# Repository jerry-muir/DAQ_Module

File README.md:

# Data Acquisition Module

## About
An exploration of Data Acquisition using Arduino based HW. In this case, the Atmega32u4 microcontroller.
This prototype consists of a custom USB connected board along with firmware and user interface software.

## The Project

Hardware design files are located at: [Hardware](/Hardware)
<br />
Arduino sketch firmware design files are located at: [Basic DAQ](/Software/Embedded/Arduino/DAQ%20Module/Basic%20DAQ)
<br />
Desktop Software design files are located at:  [BDAQ-6104 Instrument Driver](/Software/LabView/BDAQ-6104%20Instrument%20Driver)

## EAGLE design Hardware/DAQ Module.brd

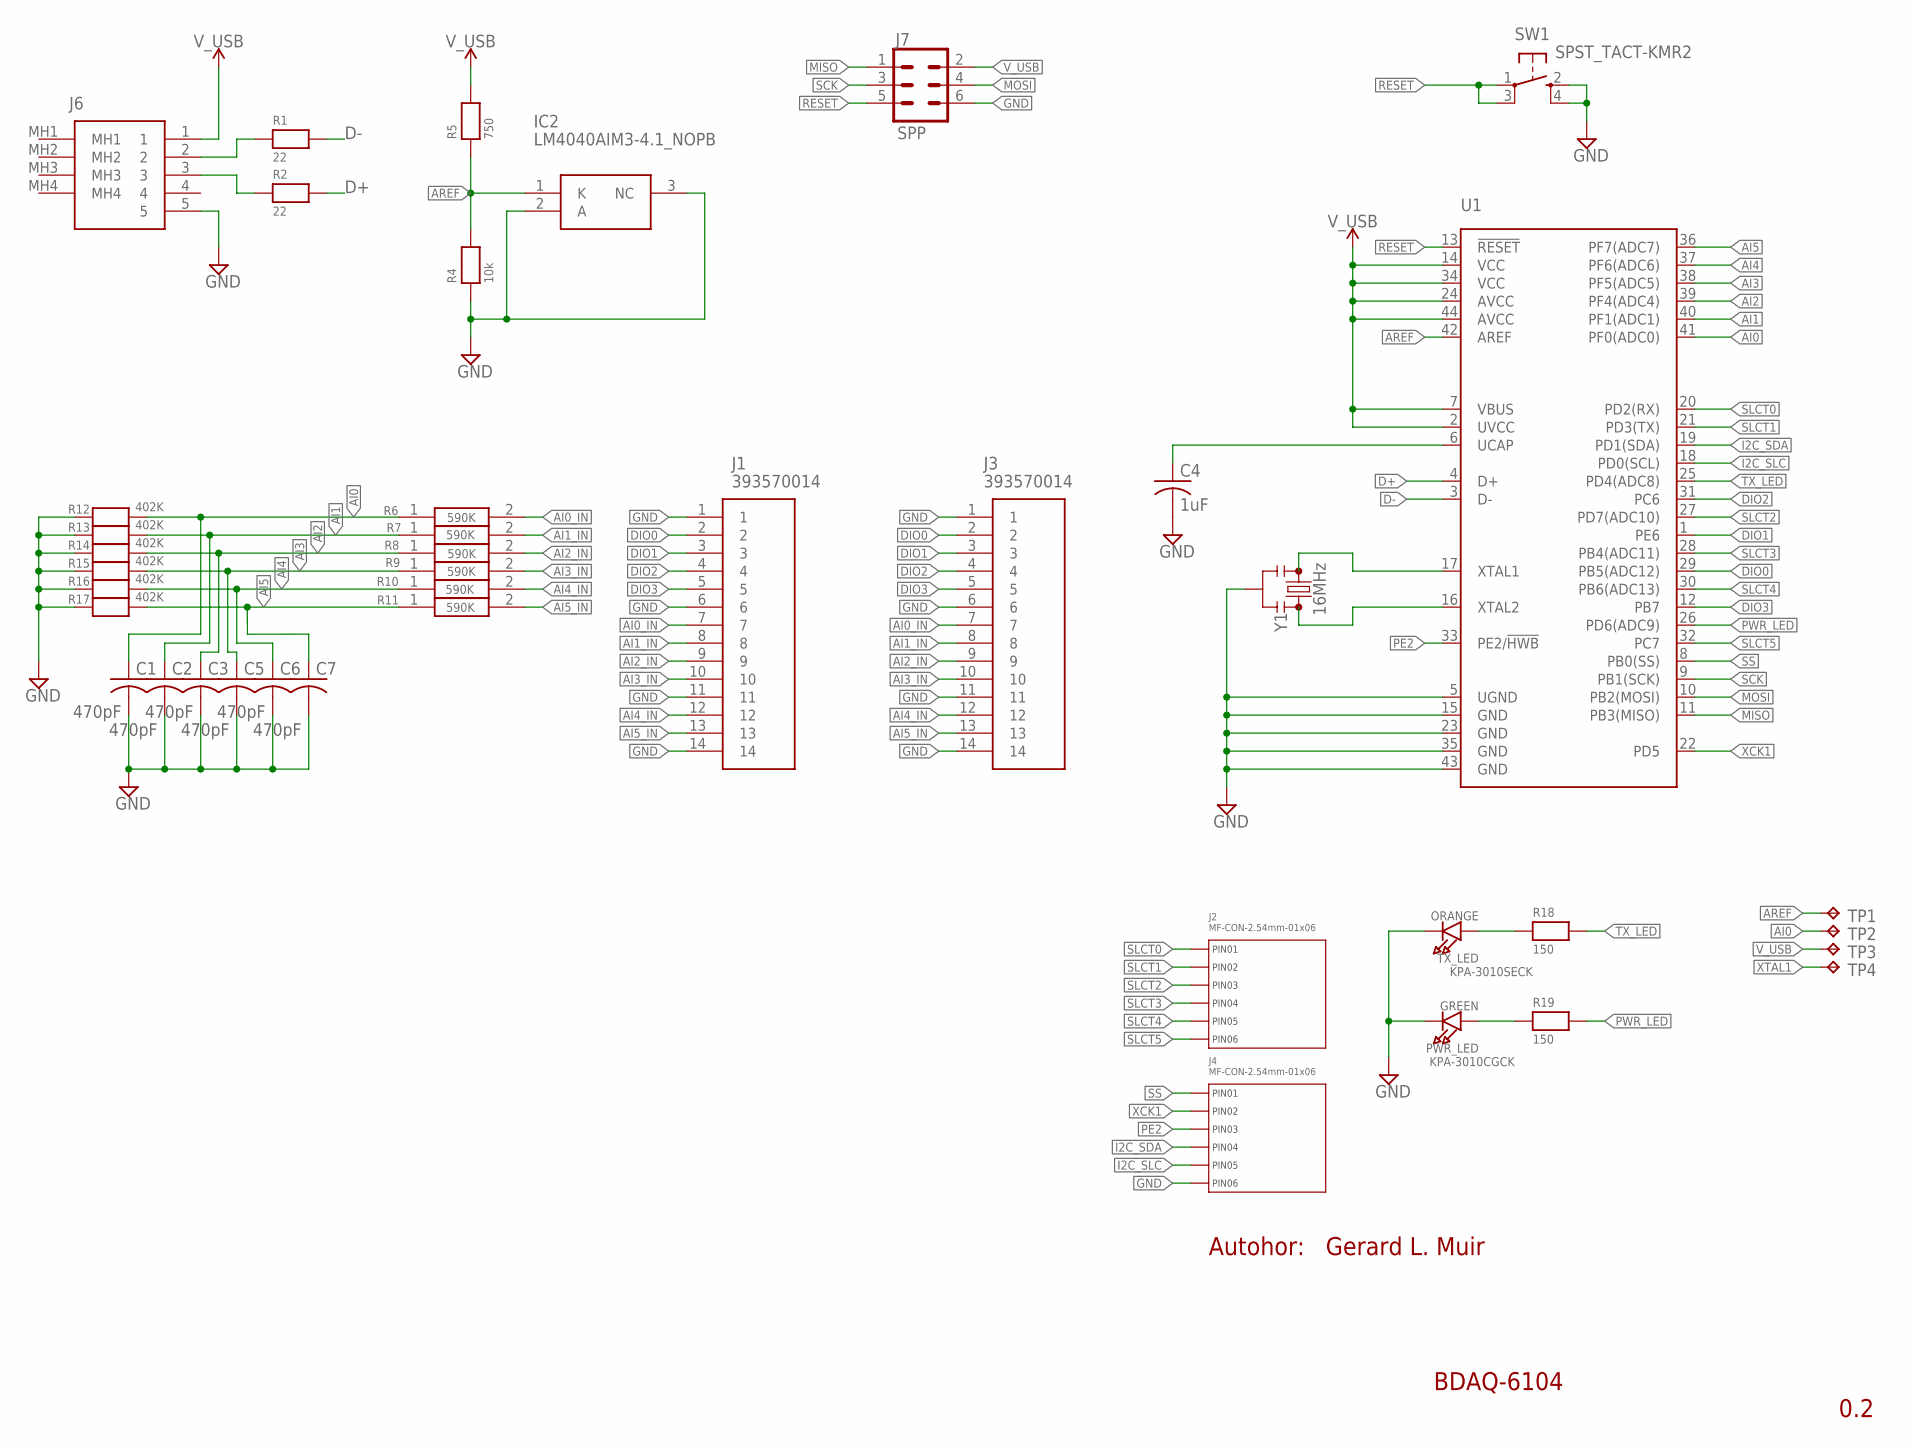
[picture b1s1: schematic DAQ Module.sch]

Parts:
C1, C2, C3, C5, C6, C7: 470pF; C1206; MANUFACTURER_PART C1206C471J5GACTU
C4: 1uF; C1206; MANUFACTURER_PART C3216X7R1E105K085AACopied
IC2: LM4040AIM3-4.1_NOPB; SOT95P237X112-3N
J1: 393570014; RHDR16W90P0X350_1X14_5600X729X
J2, J4: MF-CON-2.54mm-01x06; PTH_2.54MM_01X06
J3: 393570014; 393570014X350_1X14
J6: UJ2-MIBH2-4-SMT-TR; UJ2MIBH24SMTTR
J7: SPP; 2X3
PWR_LED: GREEN; CHIPLED_1206; MANUFACTURER_PART KPA-3010CGCK
R1: 22; 1206; MANUFACTURER_PART ERJ8ENF22R0V
R2: 22; 1206
R4: 10k; 1206; MANUFACTURER_PART RP1206BRD075K1L
R5: 750; 1206; MANUFACTURER_PART MC009121
R6, R7, R8, R9, R10, R11: 590K; RESC1608X55N; MANUFACTURER_PART RNCS1206BKE1M00
R12, R13, R14, R15, R16, R17: 402K; 1206; MANUFACTURER_PART MCWF12R4023BTL
R18: 150; 1206; MANUFACTURER_PART CRCW1206150RFKEA
R19: 150; 1206
SW1: SPST_TACT-KMR2; KMR2; MANUFACTURER_PART KMR221G LFS
TP1, TP2, TP3, TP4: TPB1,27; B1,27
TX_LED: ORANGE; CHIPLED_1206; MANUFACTURER_PART KPA-3010SECK
U1: ATMEGA32U4TQFP; SPARKFUN-DIGITALIC_TQFP44; MANUFACTURER_PART ATMEGA32U4-AU
Y1: 16MHz; RESONATOR-SMD-3.2X1.3; MANUFACTURER_PART CSTNE16M0V530000R0

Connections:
AI0: C1.1, R6.1, R12.2, TP2.TP, U1.41 (PF0(ADC0))
AI0_IN: J1.7, J3.7, R6.2
AI1: C2.1, R7.1, R13.2, U1.40 (PF1(ADC1))
AI1_IN: J1.8, J3.8, R7.2
AI2: C3.1, R8.1, R14.2, U1.39 (PF4(ADC4))
AI2_IN: J1.9, J3.9, R8.2
AI3: C5.1, R9.1, R15.2, U1.38 (PF5(ADC5))
AI3_IN: J1.10, J3.10, R9.2
AI4: C6.1, R10.1, R16.2, U1.37 (PF6(ADC6))
AI4_IN: J1.12, J3.12, R10.2
AI5: C7.1, R11.1, R17.2, U1.36 (PF7(ADC7))
AI5_IN: J1.13, J3.13, R11.2
AREF: IC2.1 (K), R4.2, R5.1, TP1.TP, U1.42 (AREF)
D+: R2.2, U1.4 (D+)
D-: R1.2, U1.3 (D-)
DIO0: J1.2, J3.2, U1.29 (PB5(ADC12))
DIO1: J1.3, J3.3, U1.1 (PE6)
DIO2: J1.4, J3.4, U1.31 (PC6)
DIO3: J1.5, J3.5, U1.12 (PB7)
GND: C1.2, C2.2, C3.2, C4.2, C5.2, C6.2, C7.2, IC2.2 (A), IC2.3 (NC), J1.1, J1.6, J1.11, J1.14, J3.1, J3.6, J3.11, J3.14, J4.P$6 (PIN6), J6.5, J7.6, PWR_LED.C, R4.1, R12.1, R13.1, R14.1, R15.1, R16.1, R17.1, SW1.2 (S), SW1.4 (S1), TX_LED.C, U1.5 (UGND), U1.15 (GND), U1.23 (GND), U1.35 (GND), U1.43 (GND), Y1.2
I2C_SDA: J4.P$4 (PIN4), U1.19 (PD1(SDA))
I2C_SLC: J4.P$5 (PIN5), U1.18 (PD0(SCL))
MISO: J7.1, U1.11 (PB3(MISO))
MOSI: J7.4, U1.10 (PB2(MOSI))
unnamed: J6.2, R1.1
unnamed: J6.3, R2.1
unnamed: C4.1, U1.6 (UCAP)
unnamed: R18.1, TX_LED.A
unnamed: PWR_LED.A, R19.1
PE2: J4.P$3 (PIN3), U1.33 (PE2/!HWB)
PWR_LED: R19.2, U1.26 (PD6(ADC9))
RESET: J7.5, SW1.1, SW1.3 (P1), U1.13 (!RESET)
SCK: J7.3, U1.9 (PB1(SCK))
SLCT0: J2.P$1 (PIN1), U1.20 (PD2(RX))
SLCT1: J2.P$2 (PIN2), U1.21 (PD3(TX))
SLCT2: J2.P$3 (PIN3), U1.27 (PD7(ADC10))
SLCT3: J2.P$4 (PIN4), U1.28 (PB4(ADC11))
SLCT4: J2.P$5 (PIN5), U1.30 (PB6(ADC13))
SLCT5: J2.P$6 (PIN6), U1.32 (PC7)
SS: J4.P$1 (PIN1), U1.8 (PB0(SS))
TX_LED: R18.2, U1.25 (PD4(ADC8))
V_USB: J6.1, J7.2, R5.2, TP3.TP, U1.2 (UVCC), U1.7 (VBUS), U1.14 (VCC), U1.24 (AVCC), U1.34 (VCC), U1.44 (AVCC)
XCK1: J4.P$2 (PIN2), U1.22 (PD5)
XTAL1: TP4.TP, U1.17 (XTAL1), Y1.3
XTAL2: U1.16 (XTAL2), Y1.1

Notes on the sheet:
Gerard L. Muir
0.2
Autohor:
BDAQ-6104

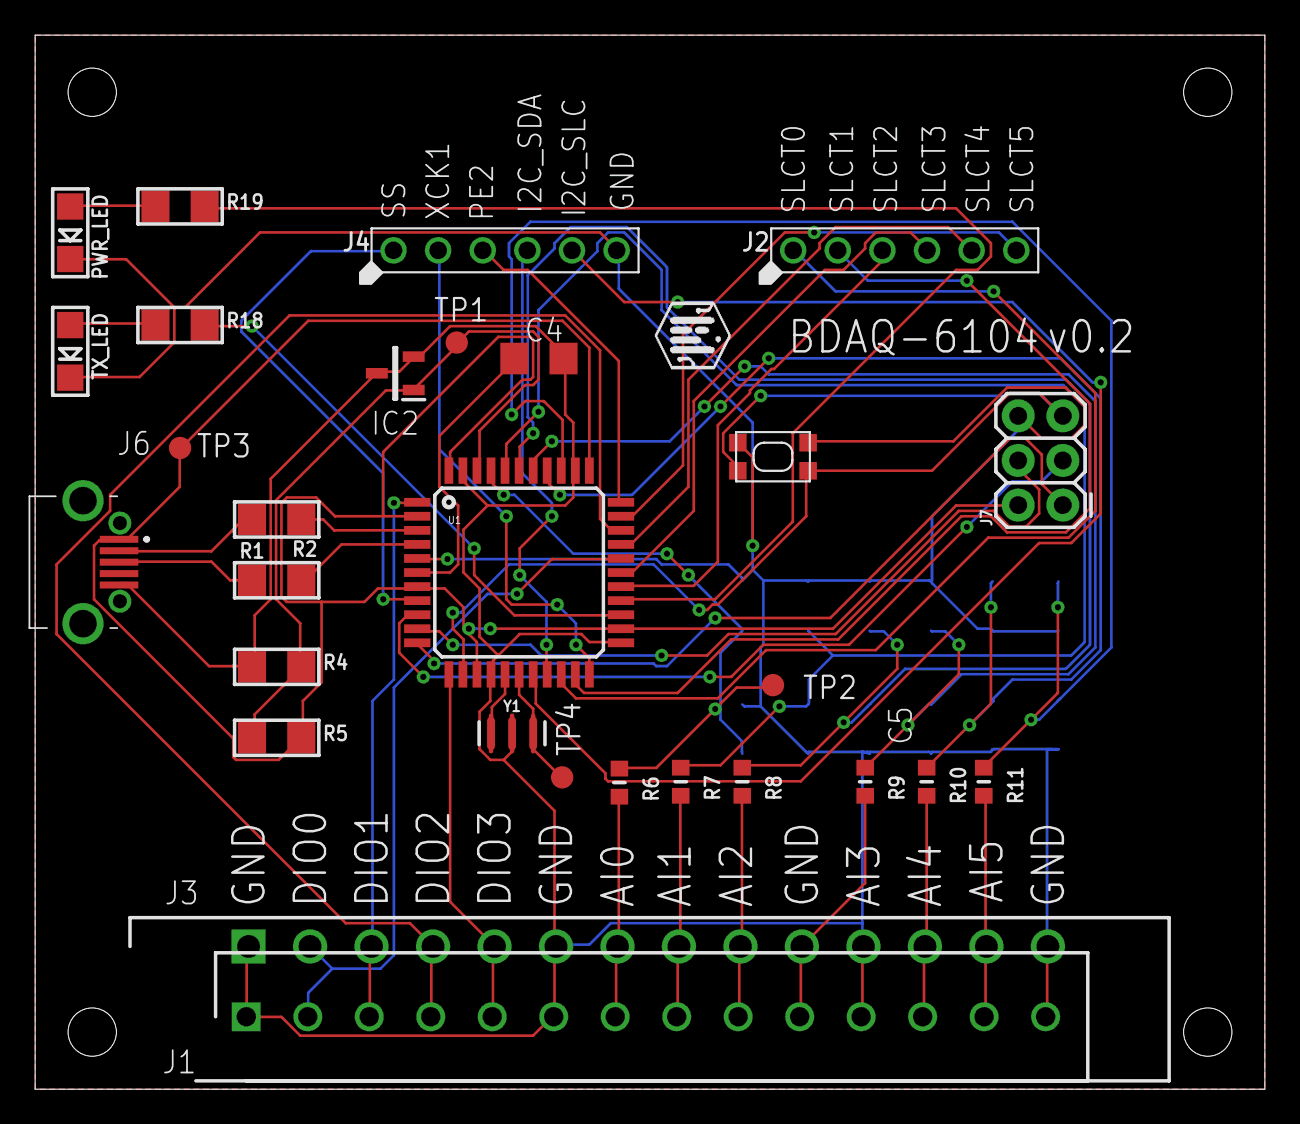
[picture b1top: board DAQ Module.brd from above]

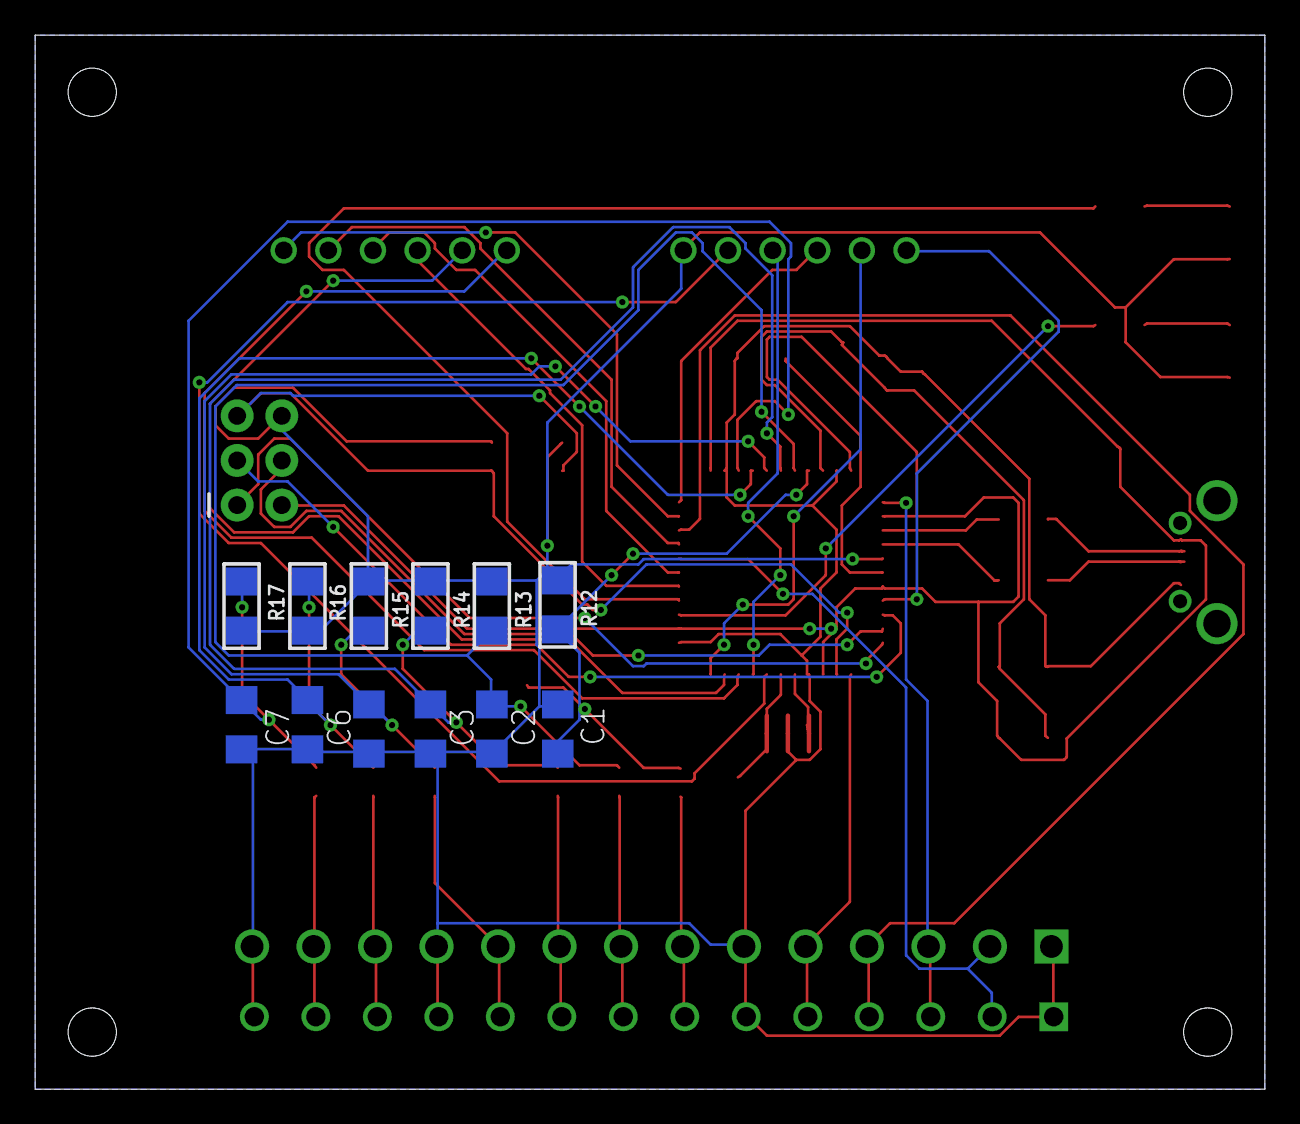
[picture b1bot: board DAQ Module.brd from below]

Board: 2 copper layers, 70.0 x 60.0 mm, 42 parts (12 on the bottom side), 45 nets.

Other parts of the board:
U$1: LOGO_TOP

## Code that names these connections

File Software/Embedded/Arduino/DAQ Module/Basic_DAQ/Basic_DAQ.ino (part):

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
// Port map.
int rx_tx = LED_BUILTIN;     // TX/RX LED on ItsyBitsy onboard LED pin 13.
int pwr_led = 12;            // Power/Status LED on ItsyBitsy D12 pin 12.
int dio0 = 9;                // Digital Input/Output dio0 on ItsyBitsy PCINT5 pin 9.
int dio1 = 7;                // Digital Input/Output dio1 on ItsyBitsy INT6 pin 7.
int dio2 = 5;                // Digital Input/Output dio2 on ItsyBitsy D5 pin 5.
int dio3 = 11;               // Digital Input/Output dio3 on ItsyBitsy on D11 pin 11.
int ai0 = 23;                // Analog Input ai0, on ItsyBitsy A5 pin 23.
int ai1 = 22;                // Analog Input ai1, on ItsyBitsy A4 pin 22.
int ai2 = 21;                // Analog Input ai2, on ItsyBitsy A3 pin 21.
int ai3 = 20;                // Analog Input ai3, on ItsyBitsy A2 pin 20.
int ai4 = 19;                // Analog Input ai4, on ItsyBitsy A1 pin 19.
int ai5 = 18;                // Analog Input ai5, on ItsyBitsy A0 pin 18.
int slct0 = 0;               // Digital Select slct0, on ItsyBitsy D0 pin 0.
int slct1 = 1;               // Digital Select slct1, on ItsyBitsy D1 pin 1.
int slct2 = 6;               // Digital Select slct2, on ItsyBitsy D6 pin 6.
int slct3 = 8;               // Digital Select slct3, on ItsyBitsy D8 pin 8.
int slct4 = 10;              // Digital Select slct4, on ItsyBitsy D10 pin 10.
int slct5 = 4;               // Digital Select slct5, on ItsyBitsy D4 pin 4.
int triggerPort = dio0;      // dio0 can alternately be used as the trigger port. 
int counterPort = dio1;      // dio1 can alternately be used as the counter port.
// Ports 14, 15, 16 (MISO, SCK, MOSI) are used for the serial programming port.
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
  // Setup and initialize IO ports.
  pinMode(rx_tx, OUTPUT);                                    // Set the LED pin as output
  pinMode(pwr_led, OUTPUT);                                  // Set the LED pin as output
  pinMode(digital_IO_Port[0], digital_IO_PortDirection[0]);  // Set the digital read pin as input
  pinMode(digital_IO_Port[1], digital_IO_PortDirection[1]);  // Set the digital read pin as input
  pinMode(digital_IO_Port[2], digital_IO_PortDirection[2]);  // Set the digital read pin as input
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
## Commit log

2025-06-23 Update README.md
    Added more details about the project design files.
2025-06-23 Update README.md
    Fixed directory references and some formatting.
2025-06-23 Initial commit.
    Initial upload of current prototype files for HW, Software and Documentation.
2025-06-23 Update README.md
    Cleaned up the directory references and project description.
2025-07-18 Hardware updates.
    - Remapping of ports for easier prototyping.
    - Addition of serial programming port.
    - New smaller board layout.
    - Higher analog imput impedance.
2025-08-06 Hardware updates and corresponding SW updates.
    - Updated analog input circuitry to use a 4.096 ARef.
    - Added analog input filtering.
    - Updated firmware to utilize new analog input circuitry.
    - Some general clean up of firmware.
    - Updated examples in LabView driver.

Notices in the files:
README.md:
License: MIT
parts and their libraries:
microbuilder: This work is placed in the public domain, and may be freely used for commercial and non-commercial work with the following conditions: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
SparkFun-Retired: Licensing: Creative Commons ShareAlike 4.0 International - https://creativecommons.org/licenses/by-sa/4.0
